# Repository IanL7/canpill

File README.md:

# canpill
Canpill is a basic development board based on Phil's Lab stm32 blue pill adaptation (https://www.youtube.com/watch?v=aVUqaB0IMh4). The board uses an STM32F103C8 microcontroller.

This repository contains the kicad project files and some basic software for the board.

## Image

- Board manufactured before R13 was added

## Additions
- A CAN transceiver with screw terminal interface
- Additional header IO breakout
- 10 pin J-Link compatible connector
- Modified layout

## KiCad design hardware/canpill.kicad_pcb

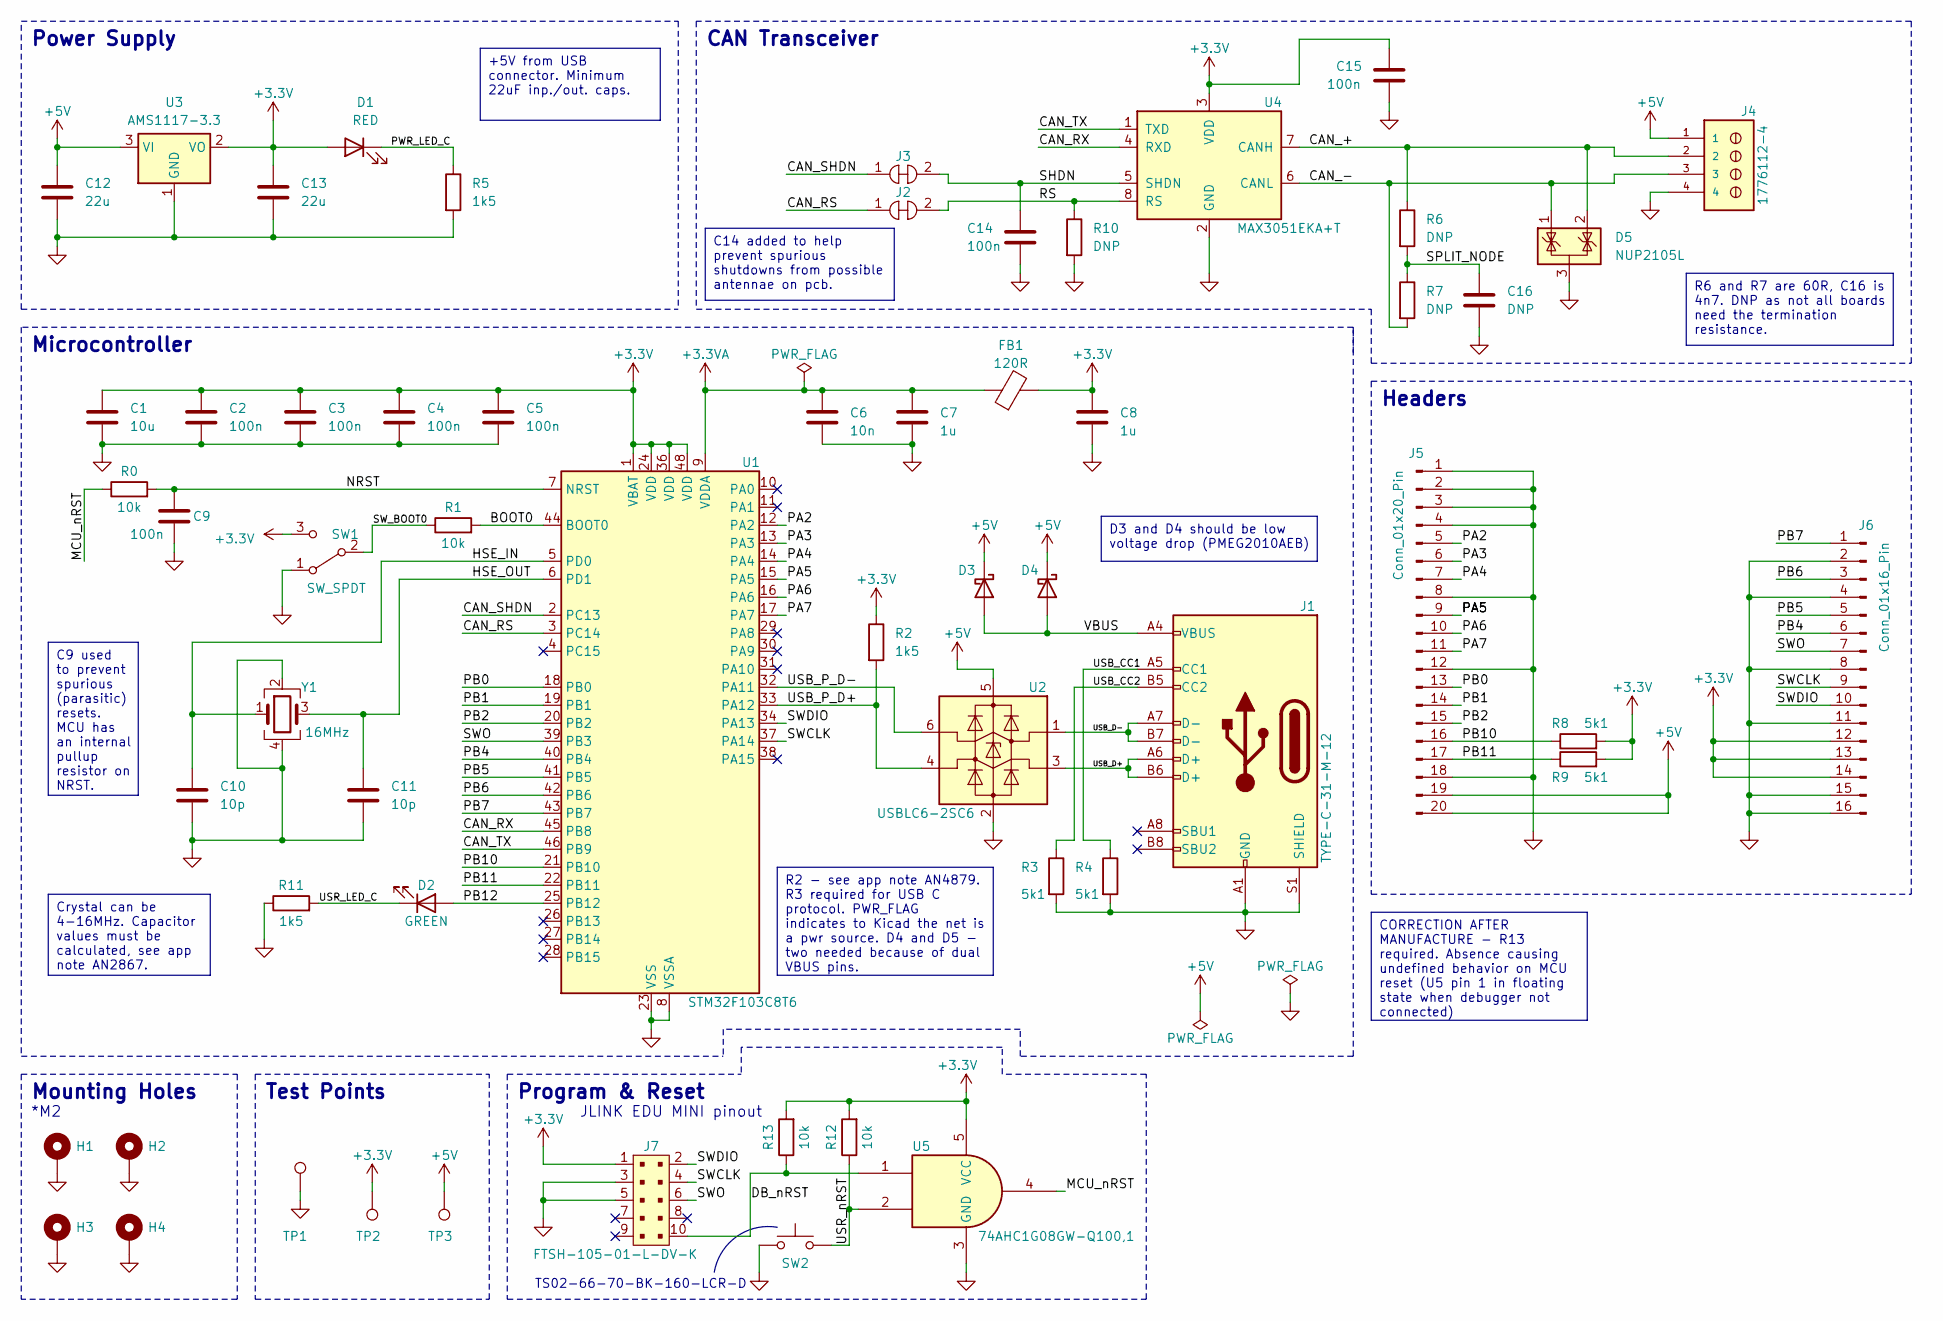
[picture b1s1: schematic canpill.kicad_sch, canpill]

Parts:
C1: 10u; C_0603_1608Metric
C2, C3, C4, C5, C9, C14, C15: 100n; C_0402_1005Metric
C6: 10n; C_0402_1005Metric
C7, C8: 1u; C_0402_1005Metric
C10, C11: 10p; C_0402_1005Metric
C12, C13: 22u; C_0805_2012Metric
C16: DNP; C_0402_1005Metric
D1: RED; LED_0603_1608Metric
D2: GREEN; LED_0603_1608Metric
D3, D4: D_Schottky; D_SOD-523
D5: NUP2105L; SOT-23
FB1: 120R; L_0603_1608Metric
H1, H2, H3, H4: MountingHole_Pad; MountingHole_2.2mm_M2_DIN965_Pad
J1: TYPE-C-31-M-12; USB_C_Receptacle_HRO_TYPE-C-31-M-12
J2, J3: 5100TR; Jumper_Micro-Miniature_P5.31mm; MPN 5100TR; Digi-Key_PN 36-5100CT-ND
J4: 1776112-4; TE_1776112-4; PARTREV R
J5: Conn_01x20_Pin; PinHeader_1x20_P2.54mm_Vertical
J6: Conn_01x16_Pin; PinHeader_1x16_P2.54mm_Vertical
J7: FTSH-105-01-L-DV-K; PinHeader_2x5_P1.27_SMD; MPN FTSH-105-01-L-DV-K; Digi-Key_PN SAM8799-ND
R0, R1, R12, R13: 10k; R_0402_1005Metric
R2, R5, R11: 1k5; R_0402_1005Metric
R3, R4, R8, R9: 5k1; R_0402_1005Metric
R6, R7: DNP; R_0402_1005Metric
R10: DNP; R_Axial_DIN0207_L6.3mm_D2.5mm_P7.62mm_Horizontal
SW1: SW_SPDT; SW_SPDT_PCM12
SW2: SW_Push; SW_PUSH_6mm
TP1, TP2, TP3: TestPoint; TestPoint_Pad_D1.0mm
U1: STM32F103C8T6; LQFP-48_7x7mm_P0.5mm
U2: USBLC6-2SC6; SOT-23-6
U3: AMS1117-3.3; SOT-223-3_TabPin2
U4: MAX3051EKA+T; SOT-23-8
U5: 74AHC1G08GW-Q100,1; SOT65P210X110-5N
Y1: 16MHz; Crystal_SMD_3225-4Pin_3.2x2.5mm

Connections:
+3.3V: C1.1, C2.1, C3.1, C4.1, C5.1, C8.1, C13.1, C15.1, D1.2 (A), FB1.2, J6.12, J6.13, J6.14, J7.1, R2.1, R8.2, R9.2, R12.2, R13.2, SW1.3 (C), TP2.1, U1.1 (VBAT), U1.24 (VDD), U1.36 (VDD), U1.48 (VDD), U3.2 (VO), U4.3 (VDD), U5.5 (VCC)
+3.3VA: C6.1, C7.1, FB1.1, U1.9 (VDDA)
+5V: C12.1, D3.1 (K), D4.1 (K), J4.1, J5.19, J5.20, TP3.1, U2.5 (VBUS), U3.3 (VI)
/BOOT0: R1.2, U1.44 (BOOT0)
/CAN_+: D5.2 (K), J4.2, R6.1, U4.7 (CANH)
/CAN_-: D5.1 (K), J4.3, R7.2, U4.6 (CANL)
/CAN_RS: J2.1, U1.3 (PC14)
/CAN_RX: U1.45 (PB8), U4.4 (RXD)
/CAN_SHDN: J3.1, U1.2 (PC13)
/CAN_TX: U1.46 (PB9), U4.1 (TXD)
/DB_nRST: J7.10, R13.1, U5.1
/HSE_IN: C10.1, U1.5 (PD0), Y1.1
/HSE_OUT: C11.1, U1.6 (PD1), Y1.3
/MCU_nRST: R0.1, U5.4
/NRST: C9.1, R0.2, U1.7 (NRST)
/PA2: J5.5, U1.12 (PA2)
/PA3: J5.6, U1.13 (PA3)
/PA4: J5.7, U1.14 (PA4)
/PA5: J5.9, U1.15 (PA5)
/PA6: J5.10, U1.16 (PA6)
/PA7: J5.11, U1.17 (PA7)
/PB0: J5.13, U1.18 (PB0)
/PB1: J5.14, U1.19 (PB1)
/PB2: J5.15, U1.20 (PB2)
/PB4: J6.6, U1.40 (PB4)
/PB5: J6.5, U1.41 (PB5)
/PB6: J6.3, U1.42 (PB6)
/PB7: J6.1, U1.43 (PB7)
/PB10: J5.16, R8.1, U1.21 (PB10)
/PB11: J5.17, R9.1, U1.22 (PB11)
/PB12: D2.2 (A), U1.25 (PB12)
/PWR_LED_C: D1.1 (K), R5.1
/RS: J2.2, R10.1, U4.8 (RS)
/SHDN: C14.1, J3.2, U4.5 (SHDN)
/SPLIT_NODE: C16.1, R6.2, R7.1
/SWCLK: J6.9, J7.4, U1.37 (PA14)
/SWDIO: J6.10, J7.2, U1.34 (PA13)
/SWO: J6.7, J7.6, U1.39 (PB3)
/SW_BOOT0: R1.1, SW1.2 (B)
/USB_CC1: J1.A5 (CC1), R4.1
/USB_CC2: J1.B5 (CC2), R3.1
/USB_D+: J1.A6 (D+), J1.B6 (D+), U2.3 (I/O1)
/USB_D-: J1.A7 (D-), J1.B7 (D-), U2.1 (I/O1)
/USB_P_D+: R2.2, U1.33 (PA12), U2.4 (I/O2)
/USB_P_D-: U1.32 (PA11), U2.6 (I/O2)
/USR_LED_C: D2.1 (K), R11.2
/USR_nRST: R12.1, SW2.2, U5.2
/VBUS: D3.2 (A), D4.2 (A), J1.A4 (VBUS), J1.A9 (VBUS), J1.B4 (VBUS), J1.B9 (VBUS)
GND: C1.2, C2.2, C3.2, C4.2, C5.2, C6.2, C7.2, C8.2, C9.2, C10.2, C11.2, C12.2, C13.2, C14.2, C15.2, C16.2, D5.3 (A), H1.1, H2.1, H3.1, H4.1, J1.A1 (GND), J1.A12 (GND), J1.B1 (GND), J1.B12 (GND), J1.S1 (SHIELD), J4.4, J5.1, J5.2, J5.3, J5.4, J5.8, J5.12, J5.18, J6.2, J6.4, J6.8, J6.11, J6.15, J6.16, J7.3, J7.5, R3.2, R4.2, R5.2, R10.2, R11.1, SW1.1 (A), SW2.1, TP1.1, U1.8 (VSSA), U1.23 (VSS), U1.35 (VSS), U1.47 (VSS), U2.2 (GND), U3.1 (GND), U4.2 (GND), U5.3 (GND), Y1.2, Y1.4

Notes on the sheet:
Crystal can be 4-16MHz. Capacitor values must be calculated, see app note AN2867.
C14 added to help prevent spurious shutdowns from possible antennae on pcb.
C9 used to prevent spurious (parasitic) resets. MCU has an internal pullup resistor on NRST.
D3 and D4 should be low voltage drop (PMEG2010AEB)
+5V from USB connector. Minimum 22uF inp./out. caps.
CORRECTION AFTER MANUFACTURE - R13 required. Absence causing undefined behavior on MCU reset (U5 pin 1 in floating state when debugger not connected)
R2 - see app note AN4879. R3 required for USB C protocol. PWR_FLAG indicates to Kicad the net is a pwr source. D4 and D5 - two needed because of dual VBUS pins.
R6 and R7 are 60R, C16 is 4n7. DNP as not all boards need the termination resistance.
Power Supply
TS02-66-70-BK-160-LCR-D
Mounting Holes
JLINK EDU MINI pinout
Headers
Microcontroller
*M2
Test Points
CAN Transceiver
Program & Reset

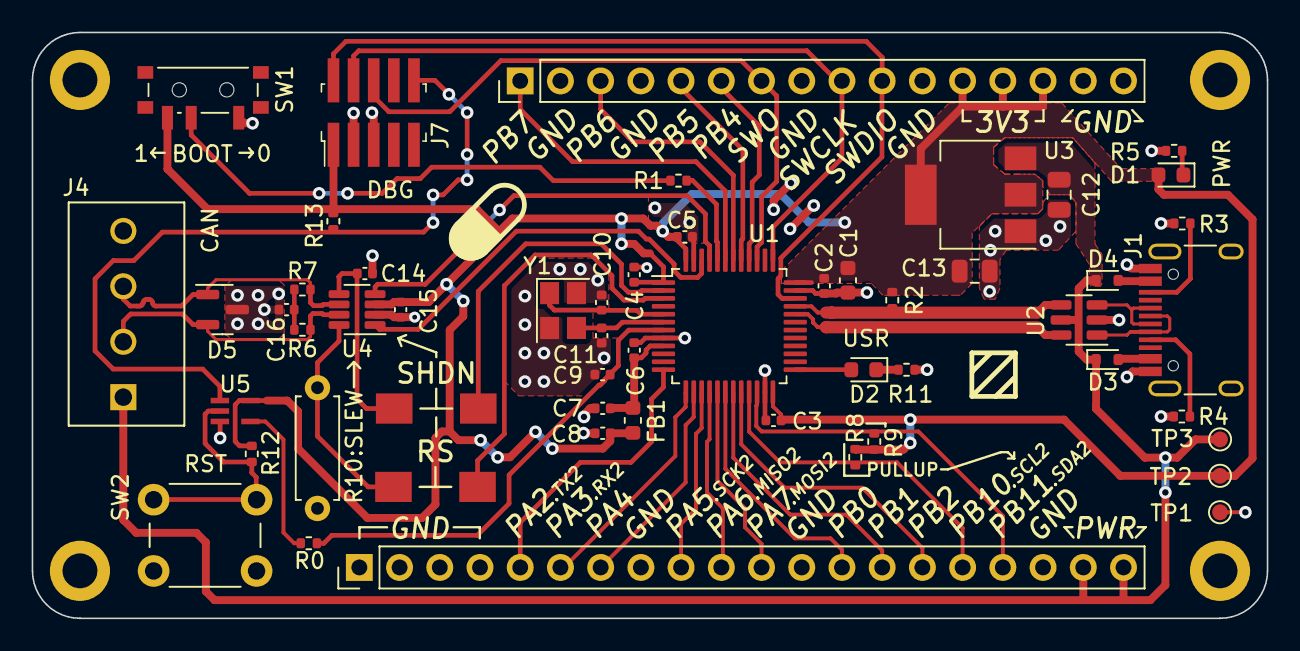
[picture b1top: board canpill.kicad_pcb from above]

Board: 2 copper layers, 78.0 x 37.0 mm, 58 parts (0 on the bottom side), 49 nets.

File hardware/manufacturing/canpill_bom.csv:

Designator,Qnty,Comment,Footprint
C1,1,10u,Capacitor_SMD:C_0603_1608Metric
"C2, C3, C4, C5, C9, C14, C15",7,100n,Capacitor_SMD:C_0402_1005Metric
C6,1,10n,Capacitor_SMD:C_0402_1005Metric
"C7, C8",2,1u,Capacitor_SMD:C_0402_1005Metric
"C10, C11",2,10p,Capacitor_SMD:C_0402_1005Metric
"C12, C13",2,22u,Capacitor_SMD:C_0805_2012Metric
D1,1,RED,LED_SMD:LED_0603_1608Metric
D2,1,GREEN,LED_SMD:LED_0603_1608Metric
"D3, D4",2,D_Schottky,Diode_SMD:D_SOD-523
D5,1,NUP2105L,Package_TO_SOT_SMD:SOT-23
FB1,1,120R,Inductor_SMD:L_0603_1608Metric
J1,1,TYPE-C-31-M-12,Connector_USB:USB_C_Receptacle_HRO_TYPE-C-31-M-12
"R0, R1, R12",3,10k,Resistor_SMD:R_0402_1005Metric
"R2, R5, R11",3,1k5,Resistor_SMD:R_0402_1005Metric
"R3, R4, R8, R9",4,5k1,Resistor_SMD:R_0402_1005Metric
SW1,1,SW_SPDT,Button_Switch_SMD:SW_SPDT_PCM12
SW2,1,SW_Push,Button_Switch_THT:SW_PUSH_6mm
"TP1, TP2, TP3",3,TestPoint,TestPoint:TestPoint_Pad_D1.0mm
U1,1,STM32F103C8T6,Package_QFP:LQFP-48_7x7mm_P0.5mm
U2,1,USBLC6-2SC6,Package_TO_SOT_SMD:SOT-23-6
U3,1,AMS1117-3.3,Package_TO_SOT_SMD:SOT-223-3_TabPin2
U4,1,MAX3051EKA+T,Package_TO_SOT_SMD:SOT-23-8
U5,1,"74AHC1G08GW-Q100,1",74AHC1G08GW_Q100_1-2:SOT65P210X110-5N
Y1,1,16MHz,Crystal:Crystal_SMD_3225-4Pin_3.2x2.5mm

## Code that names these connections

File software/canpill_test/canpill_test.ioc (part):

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Mcu.Name=STM32F103C(8-B)Tx
Mcu.Package=LQFP48
Mcu.UserName=STM32F103C8Tx
PA13.Mode=Trace_Asynchronous_SW
PA13.Signal=SYS_JTMS-SWDIO
PA14.Mode=Trace_Asynchronous_SW
PA14.Signal=SYS_JTCK-SWCLK
PB12.Signal=GPIO_Output
PB3.Mode=Trace_Asynchronous_SW
PB3.Signal=SYS_JTDO-TRACESWO
PD0-OSC_IN.Mode=HSE-External-Oscillator
PD0-OSC_IN.Signal=RCC_OSC_IN
PD1-OSC_OUT.Mode=HSE-External-Oscillator
PD1-OSC_OUT.Signal=RCC_OSC_OUT
RCC.HSEDivPLL=RCC_HSE_PREDIV_DIV2
RCC.HSE_VALUE=16000000
RCC.SYSCLKFreq_VALUE=72000000
RCC.SYSCLKSource=RCC_SYSCLKSOURCE_PLLCLK
board=custom

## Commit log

2024-05-09 add .DS_Store
2024-05-09 remove all .DS_Store files
2024-05-09 remove xml
2024-05-09 ignore backups
2024-05-14 add readme
2024-05-14 update image
2024-05-14 add microcontroller name
2024-05-14 remove logo
2024-08-07 (software:canpill_test) initial commit; (hardware) add pull-up on DB_nRST
2024-08-07 fix typo and specify mcu better
2024-08-07 convert image, add clarification to image
